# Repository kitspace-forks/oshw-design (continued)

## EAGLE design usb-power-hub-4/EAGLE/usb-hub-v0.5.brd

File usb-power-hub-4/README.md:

###4 Port USB hub
----------

####Introduction

With many low-cost linux board sitting around, getting more than 2 powered up becomes a pain since each of them require a 5V power supply! You can now power them all up and have external control over each port to turn them on/off.

This hardware allows you to connect a 5V, ___A power adapter and share it with up to 4 x USB port.

The Data (DM,DP) lines are not connected together but can be individually modified!  You can experiment with different resistor values and see if you can trigger a **samsung fast charge** or get your Iphone to recognize the charger!

**NOTE: ** You risk damaging your USB devices if the input polarity is reversed! One way to tell is to observe that the power led lights up, indicating the right polarity before inserting USB device. *You have been warned.*

**Update 05 Aug 16**

Using the resistor values from [Adafruit](https://learn.adafruit.com/assets/5973) to provide _~2.V_ on the data lines enabled apple/android charging! :)

###Power Connection

######Input
- 2.1mm diameter power jack
- microB USB
- jumper wire (+ and -)

The default power source is "selected" by the barrel jack connector with barrel jack supply as primary. microUSB will only be used if the barrel jack is unplugged.

######Output
- 4 x USB A port
- 1 x Jumper (+5v, GND)

###Signal Connection

######Input

You can individually control each USB port to turn them on/off using the **Enable** pin. Right now, the power switches chosen are **Active low** with a pull-down resistor.

######Output

Each USB power switch has a **FLAG** output that provides an open-drain output to notify users of a short/overcurrent.

You will need to add a pull-up resistor in you external circuit in order to use this.

######Casing

Oh yes, we now have a [3D-printable casing](casing) to house this useful little application and keeping the users safe from any accidental shorting!

###Lessons learnt

**V0.2 fabrication**
- Silkscreen text needs to be bigger and thicker
- Better DFM could be observed to aid future DIY repair work
- USB footprint for the through-hole is slightly too narrow. Should refer to exact datasheet measurement in future
- Visual inspection via a paper print-out before sending in order is a must. The panelized version has the connector numbering incrementing for each piece!

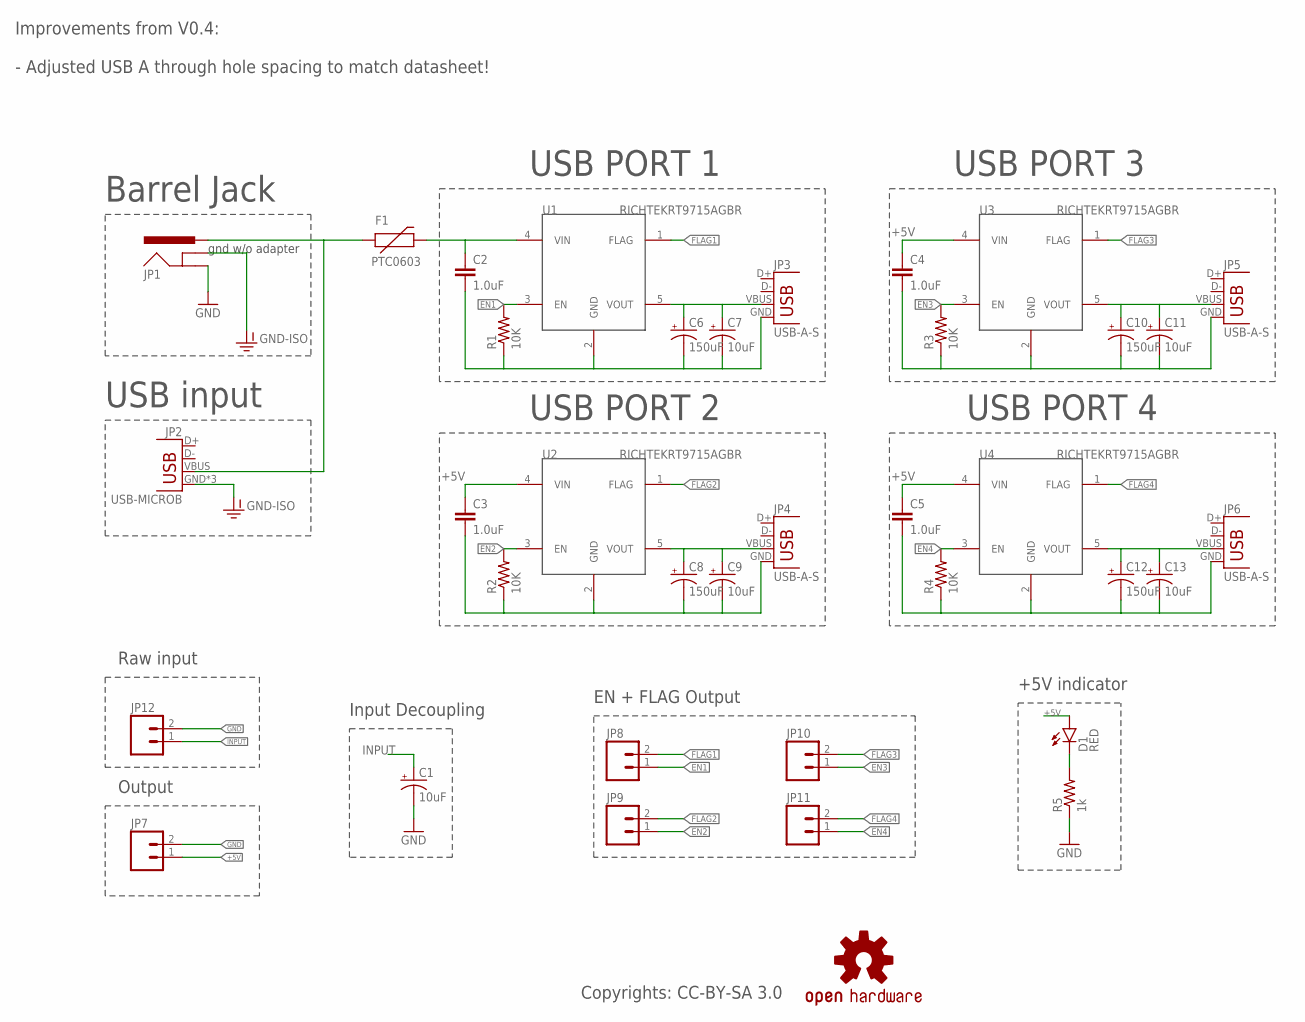
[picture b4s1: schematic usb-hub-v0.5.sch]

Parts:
C1, C7, C9, C11, C13: 10uF; EIA3216
C2, C3, C4, C5: 1.0uF; 0603-CAP
C6, C8, C10, C12: 150uF; PANASONIC_D
D1: RED; LED-0603
F1: PTC0603; 0603
JP1: POWER_JACKPTH_LOCK; POWER_JACK_PTH_LOCK
JP2: USB-MICROB
JP3, JP4, JP5, JP6: USB-A-S
JP7, JP8, JP9, JP10, JP11, JP12: M02PTH; 1X02
LOGO1: OSHW-LOGOPAD; OSHW-LOGO-M-PAD
R1, R2, R3, R4: 10K; 0402-RES
R5: 1k; 0402-RES
U1, U2, U3, U4: RICHTEKRT9715AGBR; SOT23-5

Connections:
+5V: C2.1, C3.1, C4.1, C5.1, D1.A, F1.2, JP7.1, U1.4 (VIN), U2.4 (VIN), U3.4 (VIN), U4.4 (VIN)
EN1: JP8.1, R1.2, U1.3 (EN)
EN2: JP9.1, R2.2, U2.3 (EN)
EN3: JP10.1, R3.2, U3.3 (EN)
EN4: JP11.1, R4.2, U4.3 (EN)
FLAG1: JP8.2, U1.1 (FLAG)
FLAG2: JP9.2, U2.1 (FLAG)
FLAG3: JP10.2, U3.1 (FLAG)
FLAG4: JP11.2, U4.1 (FLAG)
GND: C1.C (-), C2.2, C3.2, C4.2, C5.2, C6.-, C7.C (-), C8.-, C9.C (-), C10.-, C11.C (-), C12.-, C13.C (-), JP1.GND, JP3.GND, JP4.GND, JP5.GND, JP6.GND, JP7.2, JP12.2, R1.1, R2.1, R3.1, R4.1, R5.1, U1.2 (GND), U2.2 (GND), U3.2 (GND), U4.2 (GND)
GND-ISO: JP1.GNDBREAK, JP2.GND, JP2.MT1 (GND), JP2.MT2 (GND)
INPUT: C1.A (+), F1.1, JP1.PWR, JP2.VBUS, JP12.1
unnamed: D1.C, R5.2
VOUT1: C6.+, C7.A (+), JP3.VBUS, U1.5 (VOUT)
VOUT2: C8.+, C9.A (+), JP4.VBUS, U2.5 (VOUT)
VOUT3: C10.+, C11.A (+), JP5.VBUS, U3.5 (VOUT)
VOUT4: C12.+, C13.A (+), JP6.VBUS, U4.5 (VOUT)

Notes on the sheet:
gnd w/o adapter
USB PORT 1
USB PORT 3
USB PORT 2
USB PORT 4
Raw input
Output
Input Decoupling
Barrel Jack
USB input
EN + FLAG Output
Copyrights: CC-BY-SA 3.0
+5V indicator
Improvements from V0.4: - Adjusted USB A through hole spacing to match datasheet!

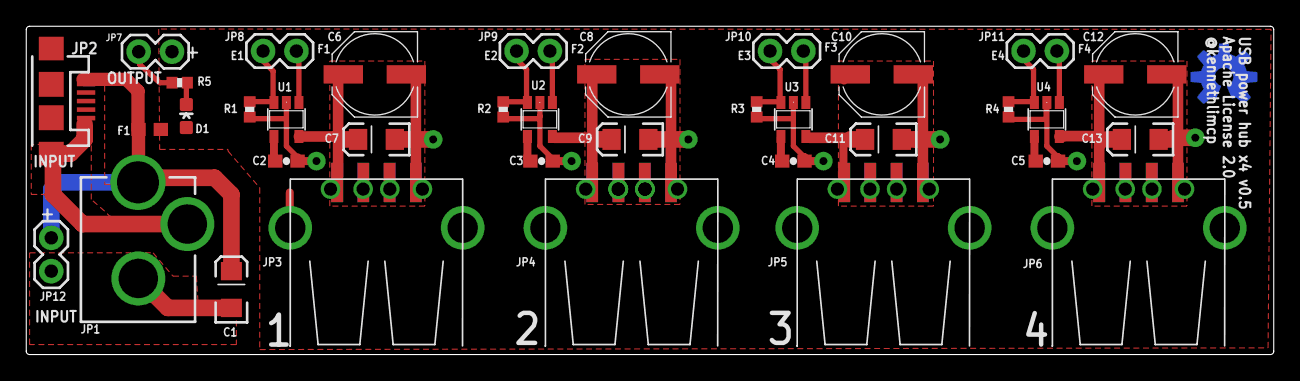
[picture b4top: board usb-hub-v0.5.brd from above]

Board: 4 copper layers, 95.0 x 25.0 mm, 37 parts (1 on the bottom side), 17 nets.

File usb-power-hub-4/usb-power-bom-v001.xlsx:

| PROJECT NAME |  | USB POWER HUB X4
 | BOM VERSION |  | v0.0.1
 |  | Critical to the PCB Design. Cannot be substituted without changes to PCB
 |  | Consigned by owner
 |  | Important to the design. Approved Vendor and P/N can be substituted with equiva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
 |  | Non-critical Component. Vendor and P/N should be determined by cost and local a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
 | Qty | Device | Minimum Specification | Package/Case | Part Designator | MFG. | MFG. PN
 | 1 | FAB PCB | Double Sided, 1.6mm, 1OZ, Electroless Nickel Immersion Gold, Green Solder Mask,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
 | 4 | ALUMINIUM ELECTROLYTIC CAPACITOR | 150uF, Alu Elec, 10V, ±20 %, ESR 0.26ohm | PANASONIC D | C6, C8, C10, C12 | PANASONIC | EEEFP1A151AP
 | 4 | MLCC CAPACITOR | 1uF, MLCC 16V, -20/+80%, Y5V | 603 | C2, C3, C4, C5 | MULTICOMP | MC0603F105Z160CT
 | 5 | TANTALUM CAPACITOR | 10uF, Tantalum 16V, 10%, ESR 3ohm | 1206 | C1, C7, C9, C11, C13 | AVX | TAJA106K016RNJ
 | 4 | RESISTOR | 10K, 5% | 0402 | R1, R2, R3, R4 | MULTICOMP | MCMR04X103 JTL
 | 1 | RESISTOR | 1K, 5% | 0402 | R5 | MULTICOMP | MCMR04X102 JTL
 | 1 | PTC RESETTABLE FUSE
 | 1 | CONNECTOR - POWER BARREL JACK | 2.1mm diameter, Power barrel jack, 1 switch | Through hole | JP1 | CUI Inc | PJ-002A
 | 1 | CONNECTOR - USBA | USB-microB, SMD, 5 pins | USB-MICROB | JP2 | FCI | 10104110-0001LF
 | 4 | CONNECTOR - USBB | USB-A PTH, 4 Pins | Through hole | JP3, JP4, JP5, JP6 | MULTICOMP | MC32593
 | 4 | HIGH-SIDE POWER SWITCH | 1.5A Limit, Active Low, 5V, USB | SOT23-5 | U1, U2, U3, U4 | RICHTEK | RT9715FGBR
 | 6 | HEADER | Single String, 0.2" Mating Length | 0.1" 02-pin | JP7, JP8, JP9, JP10, JP11, JP12 | MULTICOMP | SPC20481
 | 1 | DIODE (LED) | RED, SMD | 0603 | D1 | KINGBRIGHT | KPT-1608SURCK
 |  |  |  |  | Parts count: | 37

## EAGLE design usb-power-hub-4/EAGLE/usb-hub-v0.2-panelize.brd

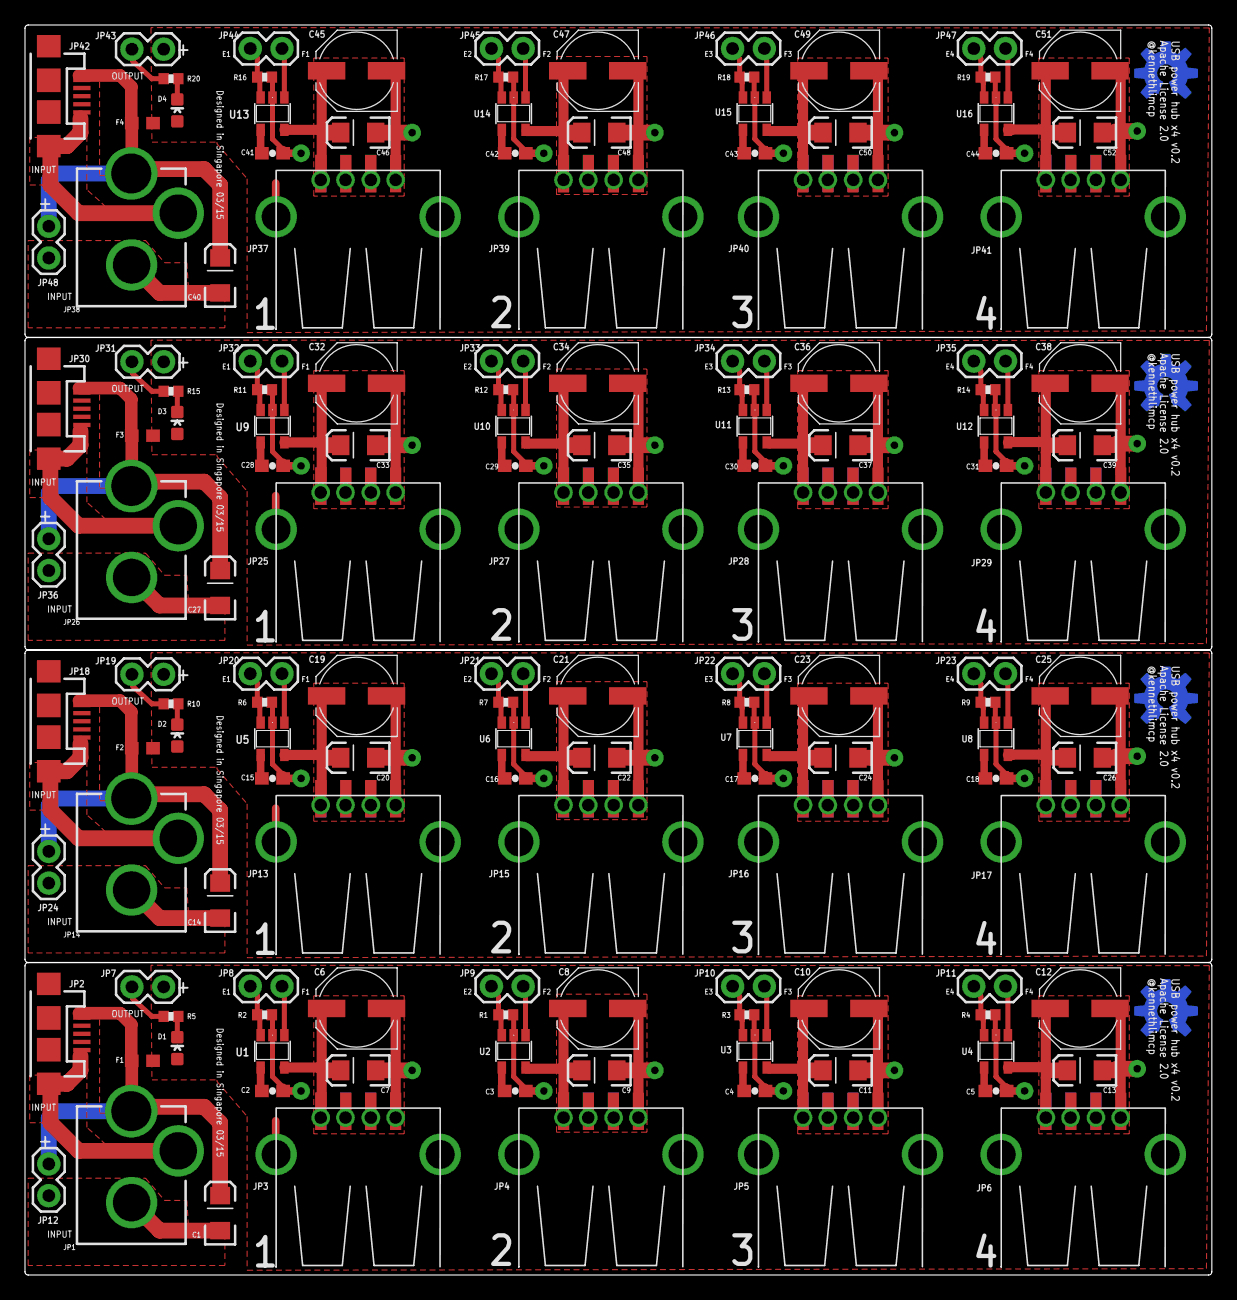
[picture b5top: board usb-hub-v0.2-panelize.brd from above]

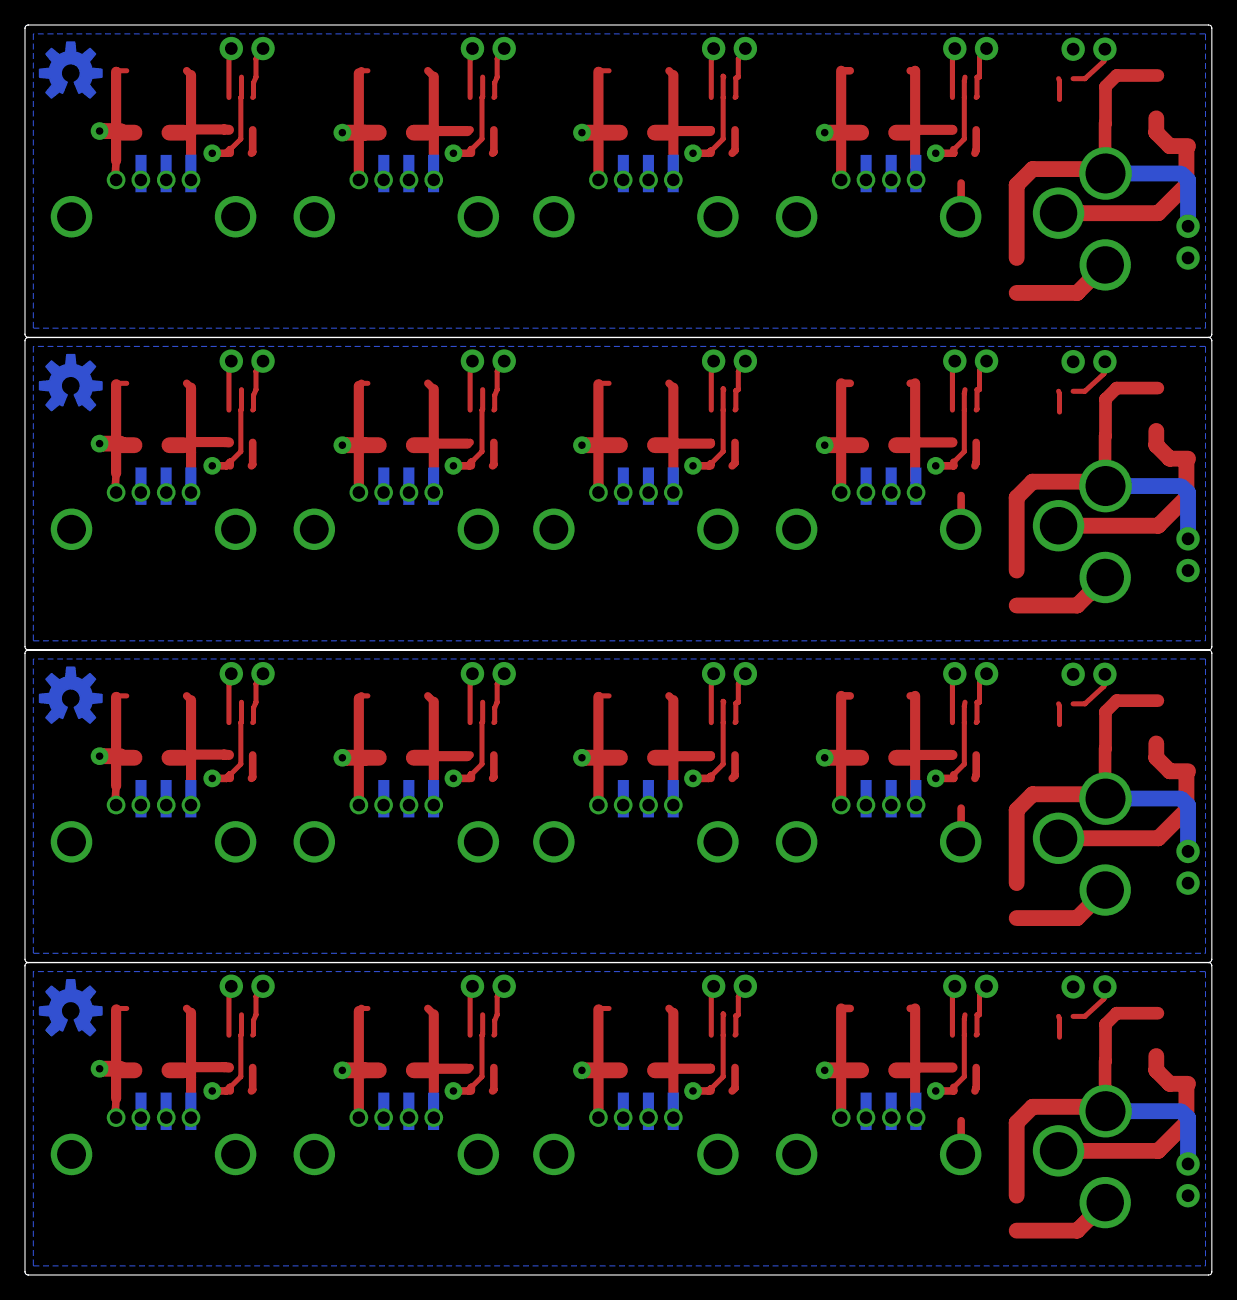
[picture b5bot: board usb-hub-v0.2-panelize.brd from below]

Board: 4 copper layers, 95.0 x 100.1 mm, 148 parts (4 on the bottom side), 68 nets.

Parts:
C1, C7, C9, C11, C13, C14, C20, C22, C24, C26, C27, C33, C35, C37, C39, C40, C46, C48, C50, C52: 10uF; EIA3216
C2, C3, C4, C5, C15, C16, C17, C18, C28, C29, C30, C31, C41, C42, C43, C44: 1.0uF; 0603-CAP
C6, C8, C10, C12, C19, C21, C23, C25, C32, C34, C36, C38, C45, C47, C49, C51: 150uF; PANASONIC_D
D1, D2, D3, D4: RED; LED-0603
F1, F2, F3, F4: PTC0603; 0603
JP1, JP14, JP26, JP38: POWER_JACKPTH_LOCK; POWER_JACK_PTH_LOCK
JP2, JP18, JP30, JP42: USB-MICROB
JP3, JP4, JP5, JP6, JP13, JP15, JP16, JP17, JP25, JP27, JP28, JP29, JP37, JP39, JP40, JP41: USB-A-S
JP7, JP8, JP9, JP10, JP11, JP12, JP19, JP20, JP21, JP22, JP23, JP24, JP31, JP32, JP33, JP34, JP35, JP36, JP43, JP44, JP45, JP46, JP47, JP48: 1X02
LOGO1, LOGO2, LOGO3, LOGO4: OSHW-LOGOPAD; OSHW-LOGO-M-PAD
R1, R2, R3, R4, R6, R7, R8, R9, R11, R12, R13, R14, R16, R17, R18, R19: 10K; 0402-RES
R5, R10, R15, R20: 0402-RES
U1, U2, U3, U4, U5, U6, U7, U8, U9, U10, U11, U12, U13, U14, U15, U16: RICHTEKRT9715AGBR; SOT23-5

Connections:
+5V: C2.1, C3.1, C4.1, C5.1, D1.A, F1.2, JP7.1, U1.4, U2.4, U3.4, U4.4
+5V1: C15.1, C16.1, C17.1, C18.1, D2.A, F2.2, JP19.1, U5.4, U6.4, U7.4, U8.4
+5V2: C28.1, C29.1, C30.1, C31.1, D3.A, F3.2, JP31.1, U9.4, U10.4, U11.4, U12.4
+5V3: C41.1, C42.1, C43.1, C44.1, D4.A, F4.2, JP43.1, U13.4, U14.4, U15.4, U16.4
EN1: JP8.1, R2.2, U1.3
EN2: JP9.1, R1.2, U2.3
EN3: JP10.1, R3.2, U3.3
EN4: JP11.1, R4.2, U4.3
EN5: JP20.1, R6.2, U5.3
EN6: JP22.1, R8.2, U7.3
EN7: JP23.1, R9.2, U8.3
EN8: JP21.1, R7.2, U6.3
EN9: JP32.1, R11.2, U9.3
EN10: JP34.1, R13.2, U11.3
EN11: JP35.1, R14.2, U12.3
EN12: JP33.1, R12.2, U10.3
EN13: JP44.1, R16.2, U13.3
EN14: JP46.1, R18.2, U15.3
EN15: JP47.1, R19.2, U16.3
EN16: JP45.1, R17.2, U14.3
FLAG1: JP8.2, U1.1
FLAG2: JP9.2, U2.1
FLAG3: JP10.2, U3.1
FLAG4: JP11.2, U4.1
FLAG5: JP20.2, U5.1
FLAG6: JP22.2, U7.1
FLAG7: JP23.2, U8.1
FLAG8: JP21.2, U6.1
FLAG9: JP32.2, U9.1
FLAG10: JP34.2, U11.1
FLAG11: JP35.2, U12.1
FLAG12: JP33.2, U10.1
FLAG13: JP44.2, U13.1
FLAG14: JP46.2, U15.1
FLAG15: JP47.2, U16.1
FLAG16: JP45.2, U14.1
GND: C1.C, C2.2, C3.2, C4.2, C5.2, C6.-, C7.C, C8.-, C9.C, C10.-, C11.C, C12.-, C13.C, JP1.GND, JP3.GND, JP4.GND, JP5.GND, JP6.GND, JP7.2, JP12.2, R1.1, R2.1, R3.1, R4.1, R5.1, U1.2, U2.2, U3.2, U4.2
GND4: C14.C, C15.2, C16.2, C17.2, C18.2, C19.-, C20.C, C21.-, C22.C, C23.-, C24.C, C25.-, C26.C, JP13.GND, JP14.GND, JP15.GND, JP16.GND, JP17.GND, JP19.2, JP24.2, R6.1, R7.1, R8.1, R9.1, R10.1, U5.2, U6.2, U7.2, U8.2
GND5: C27.C, C28.2, C29.2, C30.2, C31.2, C32.-, C33.C, C34.-, C35.C, C36.-, C37.C, C38.-, C39.C, JP25.GND, JP26.GND, JP27.GND, JP28.GND, JP29.GND, JP31.2, JP36.2, R11.1, R12.1, R13.1, R14.1, R15.1, U9.2, U10.2, U11.2, U12.2
GND6: C40.C, C41.2, C42.2, C43.2, C44.2, C45.-, C46.C, C47.-, C48.C, C49.-, C50.C, C51.-, C52.C, JP37.GND, JP38.GND, JP39.GND, JP40.GND, JP41.GND, JP43.2, JP48.2, R16.1, R17.1, R18.1, R19.1, R20.1, U13.2, U14.2, U15.2, U16.2
GND-ISO: JP1.GNDBREAK, JP2.GND, JP2.MT1, JP2.MT2
GND-ISO1: JP14.GNDBREAK, JP18.GND, JP18.MT1, JP18.MT2
GND-ISO2: JP26.GNDBREAK, JP30.GND, JP30.MT1, JP30.MT2
GND-ISO3: JP38.GNDBREAK, JP42.GND, JP42.MT1, JP42.MT2
INPUT: C1.A, F1.1, JP1.PWR, JP2.VBUS, JP12.1
INPUT1: C14.A, F2.1, JP14.PWR, JP18.VBUS, JP24.1
INPUT2: C27.A, F3.1, JP26.PWR, JP30.VBUS, JP36.1
INPUT3: C40.A, F4.1, JP38.PWR, JP42.VBUS, JP48.1
unnamed: D1.C, R5.2
unnamed: D2.C, R10.2
unnamed: D3.C, R15.2
unnamed: D4.C, R20.2
VOUT1: C6.+, C7.A, JP3.VBUS, U1.5
VOUT2: C8.+, C9.A, JP4.VBUS, U2.5
VOUT3: C10.+, C11.A, JP5.VBUS, U3.5
VOUT4: C12.+, C13.A, JP6.VBUS, U4.5
VOUT5: C19.+, C20.A, JP13.VBUS, U5.5
VOUT6: C21.+, C22.A, JP15.VBUS, U6.5
VOUT7: C23.+, C24.A, JP16.VBUS, U7.5
VOUT8: C25.+, C26.A, JP17.VBUS, U8.5
VOUT9: C32.+, C33.A, JP25.VBUS, U9.5
VOUT10: C34.+, C35.A, JP27.VBUS, U10.5
VOUT11: C36.+, C37.A, JP28.VBUS, U11.5
VOUT12: C38.+, C39.A, JP29.VBUS, U12.5
VOUT13: C45.+, C46.A, JP37.VBUS, U13.5
VOUT14: C47.+, C48.A, JP39.VBUS, U14.5
VOUT15: C49.+, C50.A, JP40.VBUS, U15.5
VOUT16: C51.+, C52.A, JP41.VBUS, U16.5

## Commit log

2015-03-15 Initial Commit!
    First oshw project featuring a 4 port USB power hub
2015-03-15 Fixed top silkscreen
2015-03-15 new resource!
    Systematic PCB verification that allows you to minimise errors before
    fabrication
2015-03-15 moved BOM to folder + version bump
    Updated BOM for PTC resettable fuse
2015-03-16 Removed V0.1 gerber + schematic
2015-03-16 V0.2 updates!
    V0.2 improvements:
    - Fixed GND vias for USB port (some were not named as GND and left
    isolated)
    - Add in silkscreen for input + output header pins (clearer for users)
    - Spaced out USB ports to have 6mm distance in between (support more
    devices)
2015-03-16 V0.2 panelized files!
    Panelized V0.2 design to fit 10cm x 10cm board (4 pieces)
2015-03-16 pdf for V0.2
    View the updated schematics without software :)
2015-03-22 V0.2 screenshots
2015-03-22 added missing R5 value
2015-03-25 Updated power-usb readme
    1.) Added warning about reversed input polarity risk
    2.) Explaining how the input power source is chosen
    3.) Added **lesson learnt** from V0.2 fabrication
    Upcoming:
    1.) V0.4 with the fixes from V0.2
    2.) Picture of the completed module in action!
2015-03-25 fixing markdown error
2015-03-26 Adding new writeup! (pcb-checks)
2015-03-26 Revert "Adding new writeup! (pcb-checks)"
    This reverts commit 8a7552ae3429cf3a89746af5d2738cbb1615d491.
2015-03-26 Revert "Revert "Adding new writeup! (pcb-checks)""
    This reverts commit 6ceb66311c71dc4e4e15cfa38c6def799a2f32c6.
2015-03-26 Fixing markdown headers
2015-03-26 grhhh...markdown again!
2015-03-30 V0.4 update!
    - Improved DFM for R1 to R4
    - Improved silkscreen text size and readibility
2015-04-01 Added product image of usb power hub!!!
2015-04-01 opps..extra "/"
2015-04-01 V0.5 update!
    Fixed an important issue of USB A through hole spacing being too
    narrow.
    This should be a golden version since first fabrication!
2015-04-01 fixed wrong via net and missing port 2 correction
    ghhhhh….
2015-04-09 3D casing baby!
    Casing for the USB power hub :)
2015-07-08 bring up notes
    This new addition contains notes on how i start off with a new project and the details like labelling convention and silkscreen sizes etc. Good for my future reference as well!
2015-07-08 Eagle useful notes
    This talks about how a user can start off a board routing at the beginning. Also some true DRC detected errors worth sharing!
2015-07-10 added polygon isolate notes
    This will increase yield for boards in general, lowering risks of unusable boards
2015-07-10 add info about unrouted ULP
    This will save time and ensure no unrouted traces are left out during checks
2015-07-19 new project - eink!
    - Adding entire folder of information
    - V0.0.2 tested but not working and a redesign is required
2016-01-04 PCB design appnote
    - http://www.e2v.com/content/uploads/2014/02/0999A.pdf
    - Design Considerations for Mixed-Signal
2016-02-11 eink: added all v020 files and misc
2016-02-11 e-ink: added sony maintenance manual
2016-02-16 added prog-adapter for SenseSG v3
2016-02-22 add: Appnote resources
2016-04-04 add: pcb design app note
2016-08-05 usb-hub: updated README.md
    Added link to Adafruit tutorial for data line voltage implementation.
2016-08-15 add: resource
2016-08-21 add: resource and bring-up notes
    - added EMC compatability appnote
    - be more specific with units
